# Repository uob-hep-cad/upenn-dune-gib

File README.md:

# DUNE Timing System GPS Interface Board (GIB) Hardware – PCB Designs

This repository contains hardware design files for DUNE Timing System GPS Interface Board (GIB)  
It includes both Cadence Allegro and KiCAD projects for different components.

---

## 📂 Repository Structure

### `allegro/`
- Contains Cadence Allegro PCB design files.  
- Used for [describe subsystem / purpose here].

### `PCB_Health/`
- KiCAD project for a small **health monitoring board**.  
- Functions:
  - Monitor **fans** and **temperature sensors**
  - Control **power rails** 
- Supports the main GIB.

---

## 🔧 Requirements

To open and work with the files, you’ll need:

- **Cadence Allegro** (for files in `allegro/`)
- **KiCAD (≥ 6.0)** (for files in `PCB_Health/`)

---

## ⚡ Getting Started

1. Clone the repository:
   ```bash
   git clone https://github.com/uob-hep-cad/upenn-dune-gib.git
	cd upenn-dune-gib
2. For the main GIB board, open the `.opj` file with Cadence Capture CIS
3. For the PCB_Health board, open the `.kicad_pro` file with KiCAD

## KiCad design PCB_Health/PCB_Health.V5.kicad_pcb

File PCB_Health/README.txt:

Manufacturing files for DUNE Timing System GIB Slow Control Board
( PCB_Health.v5 )

Files produced with KiCAD 10.0

David.Cussans@bristol.ac.uk , 9/June/26
 
Directory with Gerber artwork: Gerber.D001-25.DGA.V5 
Component placement (CSV and Gerber): PCB_Health.V5-all-pos.csv PCB_Health.V5-pnp_top.gbr PCB_Health.V5-pnp_bottom.gbr

BoM: PCB_Health.V5_BOM.xlsx

4-layer board. FR4. 1.6mm  Newbury Electronics "PCB train" stack-up

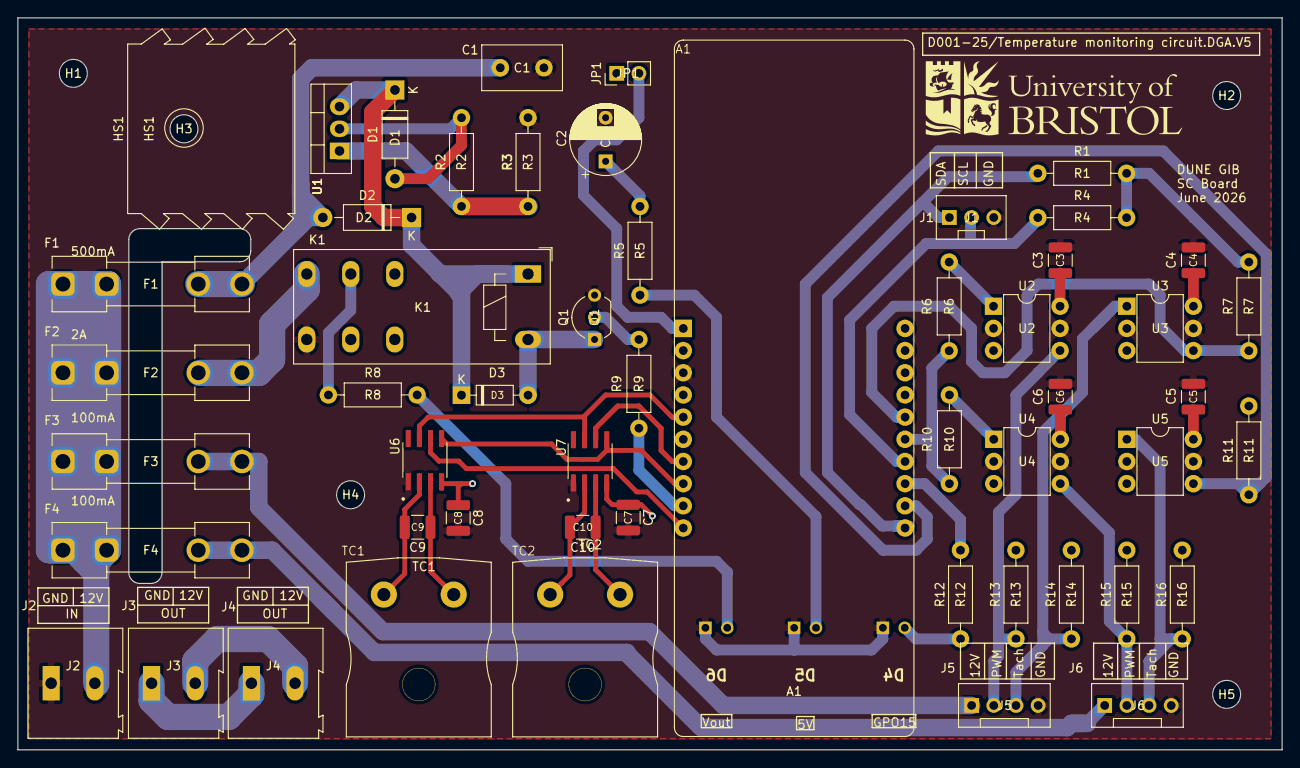
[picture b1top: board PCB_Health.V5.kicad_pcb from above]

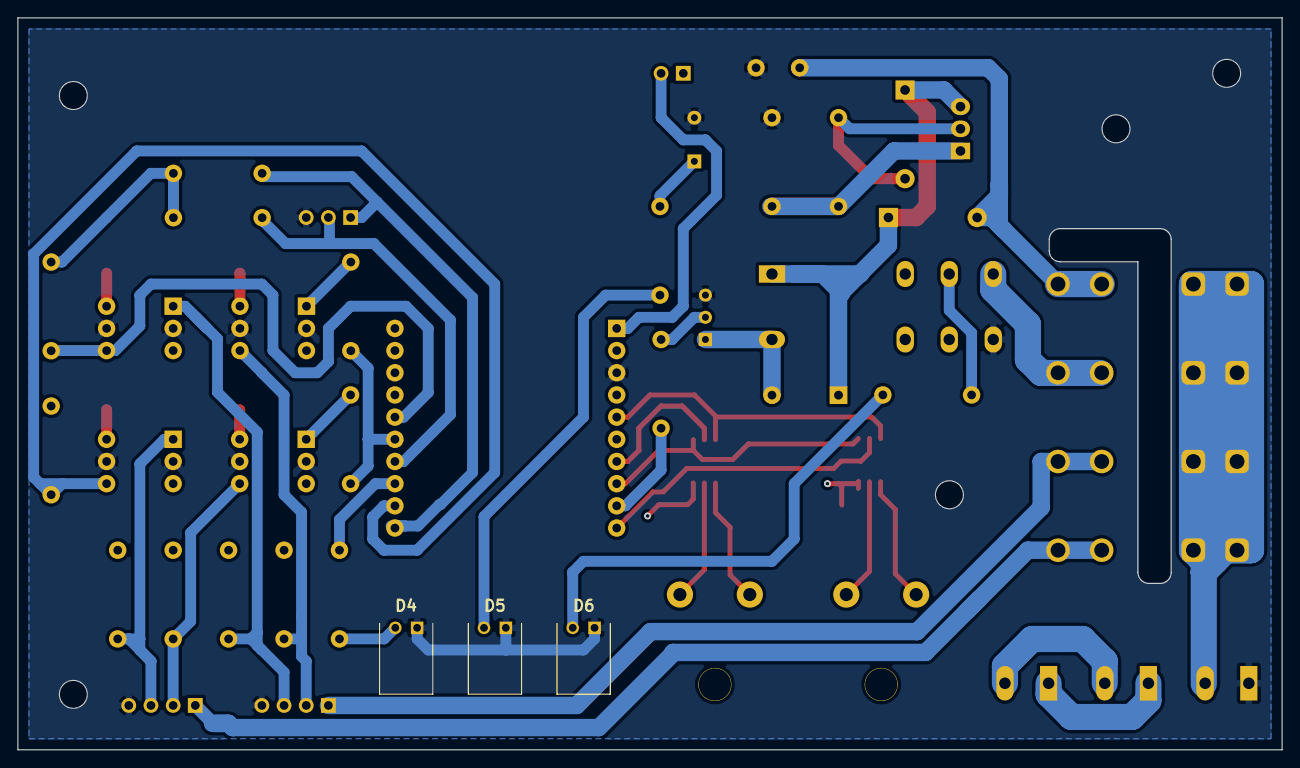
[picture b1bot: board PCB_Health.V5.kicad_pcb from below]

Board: 4 copper layers, 144.8 x 83.8 mm, 61 parts (3 on the bottom side), 39 nets.

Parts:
A1: ESP32_POE; ESP32-POE-ISO-WROVER
C1: 100n; C_Disc_D9.0mm_W5.0mm_P5.00mm
C2: 1u; CP_Radial_D8.0mm_P5.00mm
C3, C4, C5, C6, C7, C8: 100n; C_1210_3225Metric
C9, C10: 10n; C_1210_3225Metric
D1, D2: 1N4001; D_DO-41_SOD81_P10.16mm_Horizontal
D3: 1N4148; D_DO-35_SOD27_P7.62mm_Horizontal
D4, D5, D6: LED; FLPR60SG
F1: 500mA; Littelfuse 100 Spring Brass, PCB Fuse Clip for 5 x 20 mm Ca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
F2: 2A; Littelfuse 100 Spring Brass, PCB Fuse Clip for 5 x 20 mm Ca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
F3, F4: 100mA; Littelfuse 100 Spring Brass, PCB Fuse Clip for 5 x 20 mm Ca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
H1, H2, H3, H4, H5: MountingHole; MountingHole_3.2mm_M3
HS1: Heatsink; Heatsink_AAVID_TV5G_TO220_Horizontal
J1: Conn_01x03_Socket; PinHeader_1x03_P2.54mm_Vertical
J2, J3, J4: Conn_01x02_Socket; TerminalBlock_Altech_AK300-2_P5.00mm
J5: Conn_01x04_Socket; Mole_KK_1x04__Vertical
J6: Conn_01x04_Socket; PinHeader_1x04_P2.54mm_Vertical
JP1: Jumper_2_Open; PinHeader_1x02_P2.54mm_Vertical
K1: RT424012; Relay_DPDT_Schrack-RT2-FormC_RM5mm
Q1: BC337; TO-92_Inline_Wide
R1, R4, R13, R15: 10k; R_Axial_DIN0207_L6.3mm_D2.5mm_P10.16mm_Horizontal
R2: 220; R_Axial_DIN0207_L6.3mm_D2.5mm_P10.16mm_Horizontal
R3: 680; R_Axial_DIN0207_L6.3mm_D2.5mm_P10.16mm_Horizontal
R5, R7, R11, R12: 270; R_Axial_DIN0207_L6.3mm_D2.5mm_P10.16mm_Horizontal
R6, R9, R10, R14, R16: 470; R_Axial_DIN0207_L6.3mm_D2.5mm_P10.16mm_Horizontal
R8: 620; R_Axial_DIN0207_L6.3mm_D2.5mm_P10.16mm_Horizontal
TC1, TC2: Thermocouple_Alt; Thermocouple Connector
U1: LM317_TO-220; TO-220-3_Vertical
U2, U3, U4, U5: H11L1; DIP-6_W7.62mm
U6, U7: MAX6675ISA_; SOIC127P600X175-8N

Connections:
+3.3V: A1.2 (3V3), C7.1, C8.1, R1.1, R4.1, R7.2, R11.2, U6.4 (VCC), U7.4 (VCC)
+5V: C2.1, C3.1, C4.1, C5.1, C6.1, D1.2 (A), JP1.1 (A), R2.2, R5.2, R13.2, R14.2, R15.2, R16.2, U1.2 (VO), U2.6, U3.6, U4.6, U5.6
+12V: F1.1, F2.1, F3.1, F4.1, J2.2
/12: D1.1 (K), D2.1 (K), D3.1 (K), K1.A1, U1.3 (VI)
/GPIO0: A1.5 (GPIO0), U6.7 (SO), U7.7 (SO)
/GPIO2: A1.7 (GPIO2), U7.6 (~CS)
/GPIO3: A1.8 (GPIO3), U6.5 (SCK), U7.5 (SCK)
/GPIO4: A1.9 (GPIO4), R9.1
/GPIO5: A1.10 (GPIO5), U6.6 (~CS)
/GPIO13: A1.11 (GPIO13), J1.1, R1.2
/GPIO14: A1.12 (GPIO14), R11.1, U5.4
/GPIO15: A1.13 (GPIO15), R12.2
/GPIO16: A1.14 (GPIO16), J1.2, R4.2
/GPIO32: A1.15 (GPIO32), R6.2, R10.2
/GPIO33: A1.16 (GPIO33), R7.1, U3.4
/Vout: J3.2, J4.2, K1.11, R8.2
GND: A1.3 (GND), C1.2, C2.2, C3.2, C4.2, C5.2, C6.2, C7.2, C8.2, D4.1 (K), D5.1 (K), D6.1 (K), J1.3, J2.1, J5.4, J6.4, K1.24, Q1.3 (E), R3.2, U2.2, U2.5, U3.2, U3.5, U4.2, U4.5, U5.2, U5.5, U6.1 (GND), U7.1 (GND)
unnamed: A1.1 (+5V), JP1.2 (B)
unnamed: D3.2 (A), K1.A2, Q1.1 (C)
unnamed: D6.2 (A), R8.1
unnamed: D5.2 (A), R5.1
unnamed: D4.2 (A), R12.1
unnamed: C1.1, D2.2 (A), F1.2
unnamed: F2.2, K1.14
unnamed: J3.1, J4.1, K1.21
unnamed: F3.2, J5.1
unnamed: J5.2, R13.1, U2.4
unnamed: J5.3, R14.1, U3.1
unnamed: F4.2, J6.1
unnamed: J6.2, R15.1, U4.4
unnamed: J6.3, R16.1, U5.1
unnamed: Q1.2 (B), R9.2
unnamed: R6.1, U2.1
unnamed: R10.1, U4.1
unnamed: C9.1, TC1.1 (+), U6.3 (T+)
unnamed: C9.2, TC1.2 (-), U6.2 (T-)
unnamed: C10.1, TC2.1 (+), U7.3 (T+)
unnamed: C10.2, TC2.2 (-), U7.2 (T-)
unnamed: R2.1, R3.1, U1.1 (ADJ)

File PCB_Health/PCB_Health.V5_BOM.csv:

Reference,Qty,Value,DNP,Exclude from BOM,Exclude from Board,Footprint,Description,Datasheet
A1,1,ESP32_POE,,,,ESP32:ESP32-POE-ISO-WROVER,ESP32-POE-ISO-WROVER,https://cdn-learn.adafruit.com/downloads/pdf/adafruit-huzzah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
C1,1,100n,,,,Capacitor_THT:C_Disc_D9.0mm_W5.0mm_P5.00mm,Capacitor THT : C Disc D9.0mm W5.0mm P5.00mm 100n,
C2,1,1u,,,,Capacitor_THT:CP_Radial_D8.0mm_P5.00mm,Capacitor THT : CP Radial D8.0mm P5.00mm 1u,
"C3,C4,C5,C6,C7,C8",6,100n,,,,Capacitor_SMD:C_1210_3225Metric,Capacitor SMD : C 1210 3225Metric 100n,
"C9,C10",2,10n,,,,Capacitor_SMD:C_1210_3225Metric,Capacitor SMD : C 1210 3225Metric 10n,
"D1,D2",2,1N4001,,,,Diode_THT:D_DO-41_SOD81_P10.16mm_Horizontal,Diode THT : D DO-41 SOD81 P10.16mm Horizontal 1N4001,http://www.vishay.com/docs/88503/1n4001.pdf
D3,1,1N4148,,,,Diode_THT:D_DO-35_SOD27_P7.62mm_Horizontal,Diode THT : D DO-35 SOD27 P7.62mm Horizontal 1N4148,https://assets.nexperia.com/documents/data-sheet/1N4148_1N4448.pdf
"D4,D5,D6",3,LED,,,,Library:FLPR60SG, FLPR60SG,
F1,1,500mA,,,,"Library:Littelfuse 100 Spring Brass, PCB Fuse Clip for 5 x 20 mm Cartridge Fuse"," Littelfuse 100 Spring Brass, PCB Fuse Clip for 5 x 20 mm Cartridge Fuse 500mA",
F2,1,2A,,,,"Library:Littelfuse 100 Spring Brass, PCB Fuse Clip for 5 x 20 mm Cartridge Fuse"," Littelfuse 100 Spring Brass, PCB Fuse Clip for 5 x 20 mm Cartridge Fuse 2A",
"F3,F4",2,100mA,,,,"Library:Littelfuse 100 Spring Brass, PCB Fuse Clip for 5 x 20 mm Cartridge Fuse"," Littelfuse 100 Spring Brass, PCB Fuse Clip for 5 x 20 mm Cartridge Fuse 100mA",
"H1,H2,H4,H5",4,MountingHole,,,,MountingHole:MountingHole_3.2mm_M3,MountingHole : MountingHole 3.2mm M3,
HS1,1,Heatsink,,,,Heatsink:Heatsink_AAVID_TV5G_TO220_Horizontal,Heatsink : Heatsink AAVID TV5G TO220 Horizontal,
J1,1,Conn_01x03_Socket,,,,Connector_PinHeader_2.54mm:PinHeader_1x03_P2.54mm_Vertical,Connector PinHeader 2.54mm : PinHeader 1x03 P2.54mm Vertical,
"J2,J3,J4",3,Conn_01x02_Socket,,,,TerminalBlock:TerminalBlock_Altech_AK300-2_P5.00mm,TerminalBlock : TerminalBlock Altech AK300-2 P5.00mm,
J5,1,Conn_01x04_Socket,,,,Library:Mole_KK_1x04__Vertical, Molex KK 1x04  Vertical,
J6,1,Conn_01x04_Socket,,,,Connector_PinHeader_2.54mm:PinHeader_1x04_P2.54mm_Vertical,Connector PinHeader 2.54mm : PinHeader 1x04 P2.54mm Vertical,
JP1,1,Jumper_2_Open,,,,Connector_PinHeader_2.54mm:PinHeader_1x02_P2.54mm_Vertical,Connector PinHeader 2.54mm : PinHeader 1x02 P2.54mm Vertical,
K1,1,RT424012,,,,Relay_THT:Relay_DPDT_Schrack-RT2-FormC_RM5mm,Relay THT : Relay DPDT Schrack-RT2-FormC RM 5mm,http://www.te.com/commerce/DocumentDelivery/DDEController?Ac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
Q1,1,BC337,,,,Package_TO_SOT_THT:TO-92_Inline_Wide,Package TO SOT THT : TO-92 Inline Wide BC337,https://diotec.com/tl_files/diotec/files/pdf/datasheets/bc337.pdf
"R1,R4,R13,R15",4,10k,,,,Library:R_Axial_DIN0207_L6.3mm_D2.5mm_P10.16mm_Horizontal, R Axial DIN0207 L6.3mm D2.5mm P10.16mm Horizontal 10k,
R2,1,220,,,,Library:R_Axial_DIN0207_L6.3mm_D2.5mm_P10.16mm_Horizontal, R Axial DIN0207 L6.3mm D2.5mm P10.16mm Horizontal,
R3,1,680,,,,Library:R_Axial_DIN0207_L6.3mm_D2.5mm_P10.16mm_Horizontal, R Axial DIN0207 L6.3mm D2.5mm P10.16mm Horizontal,
"R5,R7,R11,R12",4,270,,,,Library:R_Axial_DIN0207_L6.3mm_D2.5mm_P10.16mm_Horizontal, R Axial DIN0207 L6.3mm D2.5mm P10.16mm Horizontal,
"R6,R9,R10,R14,R16",5,470,,,,Library:R_Axial_DIN0207_L6.3mm_D2.5mm_P10.16mm_Horizontal, R Axial DIN0207 L6.3mm D2.5mm P10.16mm Horizontal,
R8,1,620,,,,Library:R_Axial_DIN0207_L6.3mm_D2.5mm_P10.16mm_Horizontal, R Axial DIN0207 L6.3mm D2.5mm P10.16mm Horizontal,
"TC1,TC2",2,Thermocouple_Alt,,,,Connector Thermo:Thermocouple Connector,Connector Thermo : Thermocouple Connector,
U1,1,LM317_TO-220,,,,Package_TO_SOT_THT:TO-220-3_Vertical,Package TO SOT THT : TO-220-3 Vertical,http://www.ti.com/lit/ds/symlink/lm317.pdf
"U2,U3,U4,U5",4,H11L1,,,,Library:DIP-6_W7.62mm, DIP-6 W7.62mm,https://www.onsemi.com/pub/Collateral/H11L3M-D.PDF
"U6,U7",2,MAX6675ISA_,,,,MAX6675ISA_:SOIC127P600X175-8N,MAX6675ISA  : SOIC127P600X175-8N,

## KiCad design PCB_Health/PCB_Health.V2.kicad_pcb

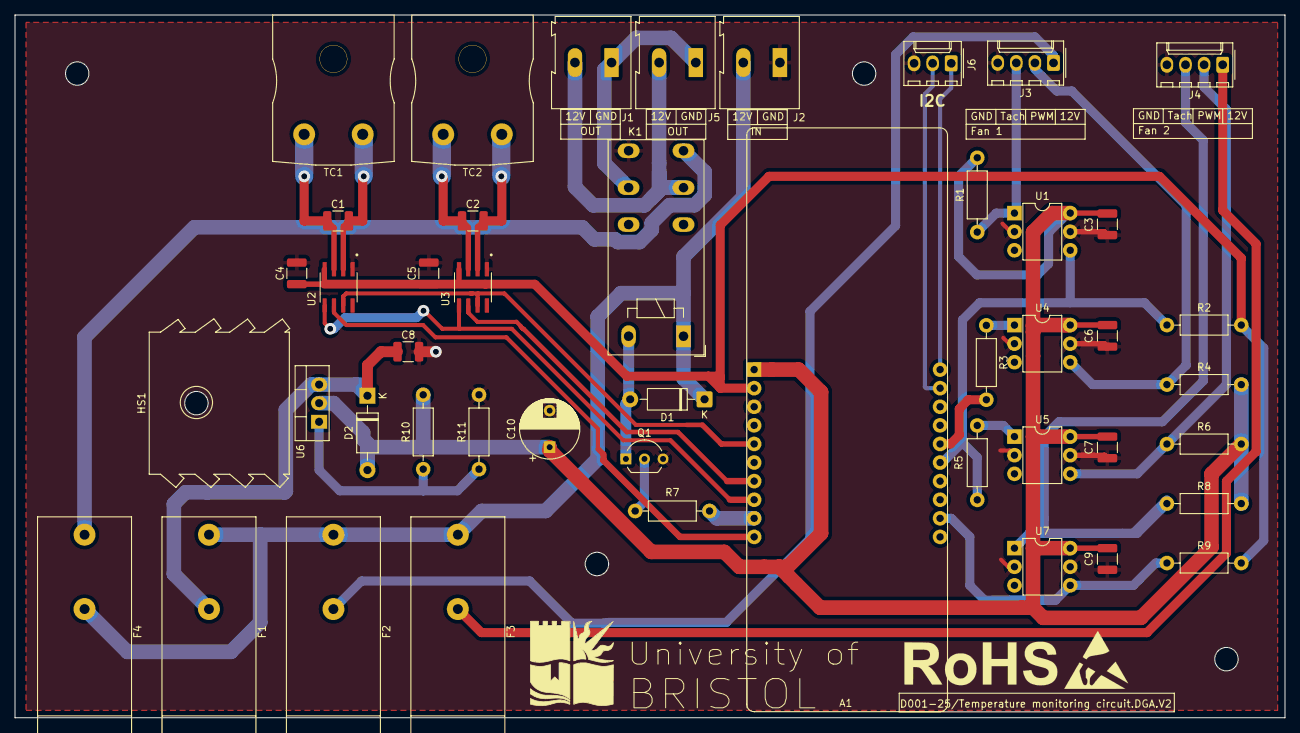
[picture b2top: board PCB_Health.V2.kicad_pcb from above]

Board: 4 copper layers, 173.5 x 96.0 mm, 51 parts (0 on the bottom side), 33 nets.

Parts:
A1: ESP32_POE; ESP32-POE-ISO-WROVER
C1, C2: 10n; C_1210_3225Metric
C3, C4, C5, C6, C7, C8, C9: 100n; C_1210_3225Metric
C10: 1u; CP_Radial_D8.0mm_P5.00mm
D1, D2: 1N4001; D_DO-41_SOD81_P10.16mm_Horizontal
F1: 500mA; Fuseholder_Cylinder-5x20mm_Bulgin_FX0457_Horizontal_Closed
F2, F3: 100mA; Fuseholder_Cylinder-5x20mm_Bulgin_FX0457_Horizontal_Closed
F4: 3A; Fuseholder_Cylinder-5x20mm_Bulgin_FX0457_Horizontal_Closed
H1, H1#2, H2, H3, H4: MountingHole; MountingHole_3.2mm_M3
HS1: Heatsink; Heatsink_AAVID_TV5G_TO220_Horizontal
J1, J2, J5: Conn_01x02_Socket; TerminalBlock_Altech_AK300-2_P5.00mm
J3, J4: Conn_01x04_Socket; Molex_KK-254_AE-6410-04A_1x04_P2.54mm_Vertical
J6: Conn_01x03_Pin; Molex_KK-254_AE-6410-03A_1x03_P2.54mm_Vertical
K1: RT424012; Relay_DPDT_Schrack-RT2-FormC_RM5mm
Q1: BC337; TO-92_Inline_Wide
R1, R3, R5, R7, R8: 470; R_Axial_DIN0207_L6.3mm_D2.5mm_P10.16mm_Horizontal
R2, R4, R6, R9: 270; R_Axial_DIN0207_L6.3mm_D2.5mm_P10.16mm_Horizontal
R10: 220; R_Axial_DIN0207_L6.3mm_D2.5mm_P10.16mm_Horizontal
R11: 680; R_Axial_DIN0207_L6.3mm_D2.5mm_P10.16mm_Horizontal
TC1, TC2: Thermocouple_Alt; Thermocouple Connector
U1, U4, U5, U7: H11L1; DIP-6_W7.62mm
U2, U3: MAX6675ISA_; SOIC127P600X175-8N
U6: LM317_TO-220; TO-220-3_Vertical

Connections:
+3.3V: A1.2 (3V3), C4.1, C5.1, R2.2, R9.2, U2.4 (VCC), U3.4 (VCC)
+5V: A1.1 (+5V), C3.1, C6.1, C7.1, C9.1, C10.1, D2.2 (A), R1.2, R4.2, R6.2, R8.2, R10.2, U1.6, U4.6, U5.6, U6.2 (VO), U7.6
+12V: D1.1 (K), F1.1, F2.1, F3.1, F4.2, J2.2, K1.A1
/GPIO0: A1.5 (GPIO0), U2.7 (SO), U3.7 (SO)
/GPIO2: A1.7 (GPIO2), U3.6 (~CS)
/GPIO3: A1.8 (GPIO3), U2.5 (SCK), U3.5 (SCK)
/GPIO4: A1.9 (GPIO4), R7.1
/GPIO5: A1.10 (GPIO5), U2.6 (~CS)
/GPIO14: A1.12 (GPIO14), R9.1, U7.4
/GPIO32: A1.15 (GPIO32), R2.1, R5.2, U1.4
/GPIO33: A1.16 (GPIO33), R3.2
/GPIO36: A1.19 (GPIO36), J6.2
/GPIO39: A1.20 (GPIO39), J6.1
GND: A1.3 (GND), C3.2, C4.2, C5.2, C6.2, C7.2, C8.2, C9.2, C10.2, J2.1, J3.4, J4.4, J6.3, K1.24, Q1.3 (E), R11.2, U1.2, U1.5, U2.1 (GND), U3.1 (GND), U4.2, U4.5, U5.2, U5.5, U7.2, U7.5
unnamed: D1.2 (A), K1.A2, Q1.1 (C)
unnamed: C8.1, D2.1 (K), F1.2, U6.3 (VI)
unnamed: F4.1, K1.14
unnamed: J1.1, J5.1, K1.21
unnamed: J1.2, J5.2, K1.11
unnamed: F2.2, J3.1
unnamed: J3.2, R4.1, U4.4
unnamed: J3.3, R1.1, U1.1
unnamed: F3.2, J4.1
unnamed: J4.2, R6.1, U5.4
unnamed: J4.3, R8.1, U7.1
unnamed: Q1.2 (B), R7.2
unnamed: R3.1, U4.1
unnamed: R5.1, U5.1
unnamed: C1.1, TC1.1 (+), U2.3 (T+)
unnamed: C1.2, TC1.2 (-), U2.2 (T-)
unnamed: C2.1, TC2.1 (+), U3.3 (T+)
unnamed: C2.2, TC2.2 (-), U3.2 (T-)
unnamed: R10.1, R11.1, U6.1 (ADJ)

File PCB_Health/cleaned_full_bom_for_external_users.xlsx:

Description | Qty per BOM | Quantity per batch | Min Quantity to order | Manufacturer | Manufacturer Part Number | Supplier | Supplier Part Number | Designator | Package Type | Technology | Comment | Status | Original Manufacturer Part No from client BOM
WiFi Development Tools - 802.11 ESP32-POE-ISO IoT development board with 100Mb 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 | 1 | 2 | 2 | Olimex Ltd. | ESP32-POE-ISO-WROVER | MOUSER | 909-P32POEISOWROVER | A1 | Standard Pack Qty | THT | ESP32_POE | Found | ESP32-POE-ISO-WROVER
Multilayer Ceramic Capacitors MLCC - SMD/SMT WCAP-CSGP 0.01uF 1210 5% 50V MLCC | 2 | 4 | 4 | Wurth Elektronik | 885012009023 | MOUSER | 710-885012009023 | C1,C2 | Cut Tape | SMD | 10n | Found | 885012009023
CAP CER 0.1UF 50V X7R 0805 | 7 | 14 | 14 | KEMET | C0805C104K5RACTU | DIGIKEY | 399-C0805C104K5RACTUCT-ND | C3,C4,C5,C6,C7,C8,C9 | Cut Tape (CT) | SMD | 100n | Found | C0805C104K5RACTU
Aluminium Electrolytic Capacitors - Radial Leaded 1.0UF 250V ELECT NHG RADIAL | 1 | 2 | 2 | Panasonic | ECA-2EHG010 | MOUSER | 667-ECA-2EHG010 | C10 | Standard Pack Qty | SMD | 1u | Found | ECA2EHG010
MULTICOMP PRO - 1N4001. - DIODE, STANDARD RECOVERY, 1A, 50V, DO-204AL-2 | 2 | 4 | 5 | MULTICOMP PRO | 1N4001. | FARNELL | 2306346 | D1,D2 | Cut Tape | THT | 1N4001 | Found | 1N4001-E3/54
PCB MNT FUSEHOLDER 5X20MM | 4 | 8 | 8 | BULGIN LTD | FX0457 | ANGLIA | 138857001 | F1,F2,F3,F4 | Bag | SMD | 500mA | Found | FX0457
Screws & Fasteners PEEK SOCKET HEAD SCREW M3 X 10 | 1 | 2 | 2 | Essentra | 183031070409 | MOUSER | 144-183031070409 | H1 | Standard Pack Qty | UNMOUNTED | Heatsink fixing | Found
BOYD - TV5G - Heat Sink, PCB, Board Level, 21.6 °C/W, TO-126, 22 mm, 19 mm, 19 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 | 1 | 2 | 2 | BOYD | TV5G | FARNELL | 170072 | HS1 | Each | SMD | Heatsink | Found | TV5G
TERMINAL BLOCK 2W | 3 | 6 | 6 | CAMDENBOSS | CTB0502/2 | ANGLIA | 1041430001 | J1,J2,J5 | Bag | THT | Conn_01x02_Socket | Found | 897-0843
Conn Wire to Board HDR 4 POS 2.54mm Solder ST Top Entry Thru-Hole KK Bag | 2 | 4 | 4 | Molex | 0022292041 | ARROW | 0323_00030517 | J3,J4 | BAG | THT | Conn_01x04_Socket | Found | 22-29-2041
Conn Wire to Board HDR 3 POS 2.54mm Solder ST Top Entry Thru-Hole KK Bag | 1 | 2 | 2 | Molex | 0022272031 | ARROW | 0323_00036827 | J6 | BAG | THT | Conn_01x03_Pin | Found | 22-27-2031
Relay: electromagnetic; DPDT; Ucoil: 12VDC; 8A; 8A/250VAC; 8A/30VDC | 1 | 2 | 2 | TE Connectivity | RT424012 | TME | RT424012 | K1 |  | THT | RT424012 | Found | RT424012
TO92 45V 0.8A 0.625W NPN | 1 | 2 | 1000 | INVAC | BC337-25 | ANGLIA | 1517347001 | Q1 | Bag | THT | BC337 | Found | BC337-25 A1
Metal Film Resistors - Through Hole 470 OHM 1/4W 1% | 5 | 10 | 10 | YAGEO | MFR-25FTE52-470R | MOUSER | 603-MFR-25FTE52-470R | R1,R3,R5,R7,R8 | Standard Pack Qty | THT | 470 | Found | MFR-25FTE52-470R
RES 270 OHM 1% 1/4W AXIAL | 4 | 8 | 8 | YAGEO | MFR-25FTE52-270R | DIGIKEY | 13-MFR-25FTE52-270RCT-ND | R2,R4,R6,R9 | Cut Tape (CT) | THT | 270 | Found | MFR-25FTE52-270R
RES 680 OHM 1% 0.6W AXIAL | 1 | 2 | 2 | TE Connectivity Passive Product | LR1F680R | DIGIKEY | A105963CT-ND | R11 | Cut Tape (CT) | SMD | 680 | Found | LR1F680R
IEC TYPE K PCB SOCKET IM-K-PCB | 2 | 4 | 4 | Labfacility Ltd | XE-1109-001 | DIGIKEY | 5425-XE-1109-001-ND | TC1,TC2 | Bag | THT | Thermocouple_Alt | Found | 304-14-320
Optocoupler Logic-Out DC-IN 1-CH 6-Pin DIP | 4 | 8 | 8 | Everlight Electronics | H11L1 | ARROW | 0323_02418914 | U1,U4,U5,U7 | BULK | SMD | H11L1 | Found | H11L1
ANALOG DEVICES - MAX6675ISA+ - Temperature Sensor IC, Digital, ± 3°C, 0 °C, 102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 | 2 | 4 | 4 | ANALOG DEVICES | MAX6675ISA+ | FARNELL | 2518704 | U2,U3 | Each | SMD | MAX6675ISA_ | Found | MAX6675ISA+
IC: voltage regulator; linear,adjustable; 1.2÷37V; 1.5A; TO220-3 | 1 | 2 | 2 | TEXAS INSTRUMENTS | LM317T/NOPB | TME | LM317T/NOPB | U6 |  | THT | LM317_TO-220 | Found | LM317T/NOPB
RES 220 OHM 1% 1/4W AXIAL | 1 | 2 | 2 | YAGEO | MFR-25FTE52-220R | DIGIKEY | 13-MFR-25FTE52-220RCT-ND | R10 | Cut Tape (CT) | THT |  | Found

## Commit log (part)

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2023-09-11 Used Tools --> Utilities --> Change path in design cache to replace [200~C:\SPB_DATA\CIS_HEP_PARTSLIB\SCHEMATIC_SYMBOLS with C:\SPB_DATA\CIS_HEP_PARTSLIB\SCHEMATIC_SYMBOLS
2023-09-11 Updating README
2023-09-11 Editing README.md
2023-09-13 Updating files with contents of GIB_v7_fab_version.zip
2023-09-13 Adding new files from GIB_v7_fab_version.zip
2023-09-20 Initial commit. About to replace all GIB v6 content
2023-09-20 Removed ADN2814 from SFP block. Created ACLK interface block ( needed editing. Updated gps_interface_boardv37.brd
2023-09-20 Added 1:2 LVDS fanout on ACLK SFP. Started to connect ACLK SFP lines
2023-09-20 Problems with export to PCB. Error about U1=1
2023-09-20 Rolling back seems to have allowed sucessful export to allegro/gps_interface_boardv37.brd
2023-09-21 Connected up ACLK_SFP_{SCL,SDA}
2023-09-21 Correcting net name
2023-09-21 FInished ref oscillator, but have unconnected pins. Starting debuggign...
2023-09-21 Deleted GBTCLK from FMC netgroup
2023-09-21 Online DRC shows very many single pin nets. Baffling
2023-09-21 Changed EEPROM to be on main I2C bus. Get same netlist error as previously
2023-09-21 Changed resistor values on GIB-MIB SFPs
2023-09-21 Changed U50,U51 to have 3.3V (rather than 3.3/5V switchable
2023-09-21 Changed U47 from sn74avc2t45 --> sn74lvc
2023-09-21 Updated PCB after changed U47 from sn74avc2t45 --> sn74lvc
2023-09-21 Got error updating PCB. Exited Capture. Will commit and restart capture
    Details: This error is displayed while running Design Differences. The error occurs due to the equal to ("=") operator being used in the reference designator (LOCATION property) value on a component.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
    ERROR(SPCODD-47): Packaging cannot be completed because the file c:\spb_data\gps_interface_board\allegro\pstxnet.dat could not be loaded. There might be syntax errors in this file. Ensure that the sy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
    ERROR(SPCODD-383): Error at line 8809 in file c:\spb_data\gps_interface
2023-09-21 Allegro crashed. Ran DBDoctor. About to try export to PCVB again
2023-09-21 Re-ran export to PCB after Allegro crash. Seemed to work OK. Have replaced barrel connector with 4-pin ATX-style 12V PC connector. Removed switch. Exported OK
2023-09-21 Added fuse to fan power supply lines
2023-09-22 Looked over schematics to make list of items to check. Added test-points to ACLK SFP I2C. Marked one of the two resistors feeding 5/3.3V level translator as DNP. Connected up enable line on Y1 (lines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
2023-09-22 Updated ROOM property on components in SFP block
2023-09-22 Tidied up SFP1 (right hand most)
2023-09-22 Created module for SFP (now without CDR)
2023-09-22 Created ROOM outlines in Allegro for SFP1 .. 6
2023-09-22 Pulled up all SFP components and used autoplace to put into ROOMs
2023-09-22 Created module (Place Replicate Create) and applied to the 6 SFPs@
2023-10-03 Adding schematic
2024-08-28 Synchronized design. Down-rev to v17.4 on /gps_interface_boardv40_quickplaced_downreved.brd
2024-08-29 Edited block diagram on first page. Printed out schematics
2024-08-29 Printed out schematics (after some considerable effort: Select top level design and use occurance mode to get correct refdes). Removed the Storage pages - which were just a dumping ground for unfinis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
2024-09-02 adjusted board file for colour preference
2024-09-05 tweaks before meeting
2024-09-05 Sourced footprint for J17 - but unable to find in schematic at moment
    Also exported all footprints/pads from Allegro board file database and set up search paths to look in dedicated folder. The RJ45 used for J17 was sourced via mouser and mapped to the pin labels being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
2024-09-05 ignore last message - found RJ45 from older board file
    Happier with source now, everything else true from previous
2024-09-06 mounting hole position rework
2024-09-19 New board stack up - lots of routing needs to be redone due to new width/sep on 100r diff trace
2024-09-20 snapshot - still lots to do on layout :(
2024-09-26 more changes to layout - getting there slowly
2024-09-27 some footprint tweaks - odd padstack origins?!
    Almost there with component placement, need to assess overall layout placement soon. Routing is getting there.
2024-10-02 another snapshot
2024-10-08 no unconnects
    Still 32 DRC errors, routing leaves a lot to be desired. Power distribution confusing at present; hopefully be able to optimise layout further.
2024-10-10 dangling lines removed etc.
    Still a few DRCs, items shifted on top edge of card - silk altered to show new posiitons
2024-10-29 Editing pins for Si5021 . Edited net names for 2.5V regulators
2024-10-29 Exiting CIS capture before merging Pete Hastings' PR
2024-10-29 Merged Pete's changes from PR31
2024-10-31 Fixed some typos in the schematic comments. Got rid of two only-one-pin-on-the net instances (on PLL output power pin and PGOOD from P5V5 regulator. Printed schematics. Produced a down-reved board fo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
2024-11-06 slowly getting through list
    just a back up for sanity's sake
2024-11-07 FOR REVIEW
2024-11-07 FOR REVIEW (AGAIN)
2024-11-07 November 2025 - been fixed to 2024
2024-11-11 smoothed attempt
2024-11-13 Need help visualising the connector mating
    I have repositioned the mounting holes on that connector but I am having a hard time visualising it mated. I have based the locations on the pc069b board file you sent to me. I believe it is correct 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
2024-11-25 Swapped the MAX9371EKA (SOT23-8) for MAX9371ESA (SOIC) . Exported to allegro/gps_interface_boardv52dc.brd
2024-11-26 last commit before sync with main
2024-12-09 latest batch of data
2025-01-13 Adding Pete's final board that was sent for production, together with the ODB++ export from it
2025-01-13 Adding updated *.brd file - added dimensions
2025-02-26 I hope this uploads
    A sanity check on a working git repo
2025-07-04 Fixed schematic errors in 2.5V and 3.3V power rails
2025-07-04 Marked relevant DNP resistors on 2.5 and 3.3V . Exported to PCB - N.B. changed r resistors became unplaced. May be disconnected. Exported placement before export to get placement back. Adding BoM for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
2025-07-07 Checked board with updated resistors. Looks OK
2025-07-07 Changed UID PROM I2C address from 0x50 --> 0x54
2025-07-08 Schematic edited to change SCL0/SDA0 to SCL_PLR/SDA_PWR on temp/voltage/current I2C monitors
2025-07-08 Moved PLL to FPGA I2C bus. Added 0.1inch header and zero ohm resistors to disconnect for debugging
2025-07-08 Moved SFP_LOS lines to FPGA on schematic. Kept TX_FLT on I2C extender. PCB needs routing
2025-07-09 Changed level translator for one that was already on the board. Export to t PCB. PCB needs layout
2025-07-09 Swapped A<-->B on U17 so that VCCA < VCCB
2025-07-09 Set IRIG input termination at DNP. Exported to PCB. No further layout needed
2025-07-09 Removed unnecssary DC-block caps to SFP. Exported to PCB. Needs layout
2025-07-09 Replaced ADN2814 with ADN2817 ( ADN2818 not recommended for new designs). Exported to PCB. Needs layout
2025-07-10 Printed out schematics will all issues resolved
2025-07-10 Replaced OR gate with fussy resistor network for LOS/TX_FAULT RED/GREEN with dual buffer with one LED on each output
2025-07-11 PCB routing done for ACLK CDR
2025-07-11 Connected up debugging header for PLL. See https://github.com/uob-hep-cad/upenn-dune-gib/issues/42
2025-07-14 Replaced device specific zero ohm links connecting SCL/A_PWR with generic 0603 zero ohm links. Ref des updated to R3699/R3700. See https://github.com/uob-hep-cad/upenn-dune-gib/issues/40
2025-07-16 SFPs in position and fixed. Light Pipe LEDS in position and fixed. Starting layout of driver chips
2025-07-18 placed and routed all status LED driver chips. Corected placement of LEDS for SFP 7: moved SPF7 statud LEDS to under SFP light pipes. Moved CDR status LEDS to nearby location.
2025-07-18 SFP TX_Fault and LOS lines somewhat untangled and rerouted. Still a bit messy but connectivity is there.
2025-07-21 FMC routing finished. I2C routing WIP
2025-07-21 I2C routing done
2025-07-21 U19 connections routed. Rotated U19 to make layout much easier.
2025-07-21 Last commit had wrong info in commit message. Should be: U17 routing done Rotated to make routing easier
2025-07-21 misc edits, all unrouted tracks done except for outstanding query with U110. Planes extended to bring 5v to U10 & U13
2025-07-21 fixed shorting error with FMC0 LOS signal at FMC connector breakout.
2025-07-21 last 2 trivial shorting errors fixed.
2025-07-21 Keepout DRCs waived: SFP cages only need route keepout zones on top layer. We can allow tracks on other layers.
2025-07-21 Track to Via DRCs fixed
2025-07-22 Package-Package spacing DRCs fixed. Except for two testpoints. Can't see how to set a waiver for this.
2025-07-22 Corrected SCH around U110 - Connected pins 2, 10, & 12 to Vcc. Layout updates WIP
2025-07-23 Changed Constraints Manager to enforce correct Diff Pair track/gaps. Was set up as Electrical rule which applies same constraints to all layers. Changed to use Physical constraint which can apply dif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
2025-07-23 all DRCs claersed relating to tracking, diff pairs etc. Just one package-Package left to waive.
2025-07-23 ALL DRCs CLEARED.
2025-07-23 Silkscreen tidy up WIP
2025-07-24 various cosmetic edits to Top silkscreen layers
2025-07-24 various edits to Top Assembly drawing
2025-07-24 various edits to Bottom Assembly drawing
2025-07-24 improved positioning of I2C testpoints and tidied up routing, silkscreens etc. Have a weird DRC error to troubleshoot
2025-07-25 fixed weird DRC issue. DRCs all ok
2025-07-25 improved layout of VCC2V5 current sense resistor
2025-07-25 improved layout of 3V3 regulator outputs, current sharing resistors, current shunt and monitoring IC
2025-07-25 improved layout of 5V current shunt and monitoring IC
2025-07-25 added more vias to high current output of L6 (VP3V5)
2025-07-25 trivial changes, moved some test points, added some silkscreen text etc
2025-07-25 Added GND pour to routing layers for copper balance. Edited silkscreen to say GIB V.3
2025-07-28 increased clearane from GND pours to 10thou from pads/vias. deleted islands.
2025-07-28 ready for review and manufacture
2025-07-29 added pdfs of schematic
2025-07-31 rotated TX_FAULT and CDS_LOL LEDs. Corrected in SCH and BRD. Tidied up silkscreens and assy dwgs to match
2025-07-31 Changed U49 address to 0x53 in SCH and BRD
2025-08-01 added teadrops & fillets
2025-08-01 added layer markers and stacking/layer visibility tabs
2025-08-01 tidied up plane edges to have consistent pullback from board edge. Fixed some isolated shapes.
2025-08-13 Editing BoM to format for PCBTrain upload tool. And addressing numerous issues - see GitHub issues log. Still WIP
2025-08-13 more BoM edits done & submitted for quote
2025-08-20 Removed LTC6957 from GPS clock input and replaced with LTC6954 comparator and LVDS fanout. Will change IRIGB input to use the same comparator
2025-08-20 Proof-of-concept layout of replacing LTC6957 iwth LTC6754 (https://github.com/uob-hep-cad/upenn-dune-gib/issues/67), removed redundant vcc3v3_lfilt ( https://github.com/uob-hep-cad/upenn-dune-gib/iss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
2025-08-20 Printed out schematic to gps_interface_board_20aug25.pdf
2025-08-21 Added pull-down resistors on unused level translator channels ( due to removed FILT_A, FILT_B, GPS_CLK_EN ). Added some NC markers on MAX9371 translators
2025-08-21 ripped up old input IC tracking etc. Started placing new components.
2025-08-22 some routing done. WIP
2025-08-28 various layout done. Still need to update silkscreens etc and wade through BOM
2025-09-02 Outputted gerbers, placement, drill file etc. Edited BoM to be up to date with changes. Submitted for manufacture as v101
2025-09-02 added some files that didn't get committed last time
2025-10-08 Added v2 files
2025-10-09 Creating Fab and assy outputs for PCB_Health board
2026-01-20 Pushing changes before switching back to GIB main PCB branch
2026-05-11 Updated design to V4 ( KiCAD project = PCB_Health.V4.kicad_pro
2026-06-09 Adding files updated by David G.A.
2026-06-09 Tidied up BoM using Newbury online tool
